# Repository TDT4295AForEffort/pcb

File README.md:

# pcb
The greenest pcb in the west

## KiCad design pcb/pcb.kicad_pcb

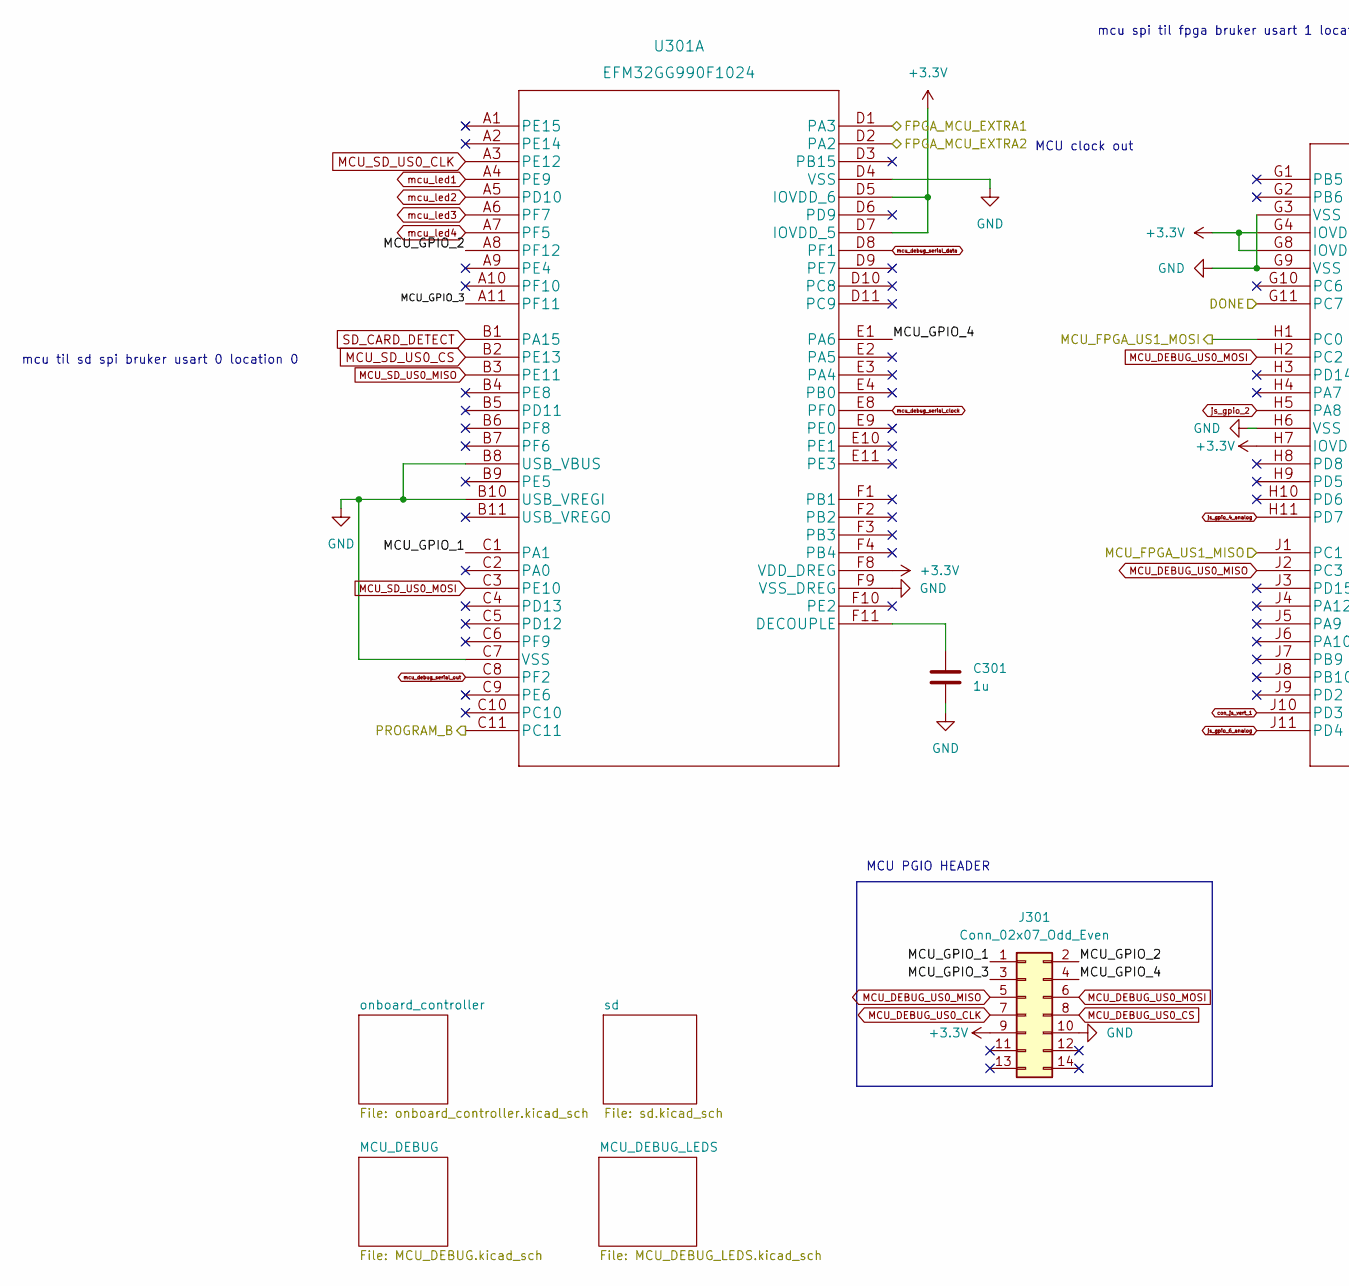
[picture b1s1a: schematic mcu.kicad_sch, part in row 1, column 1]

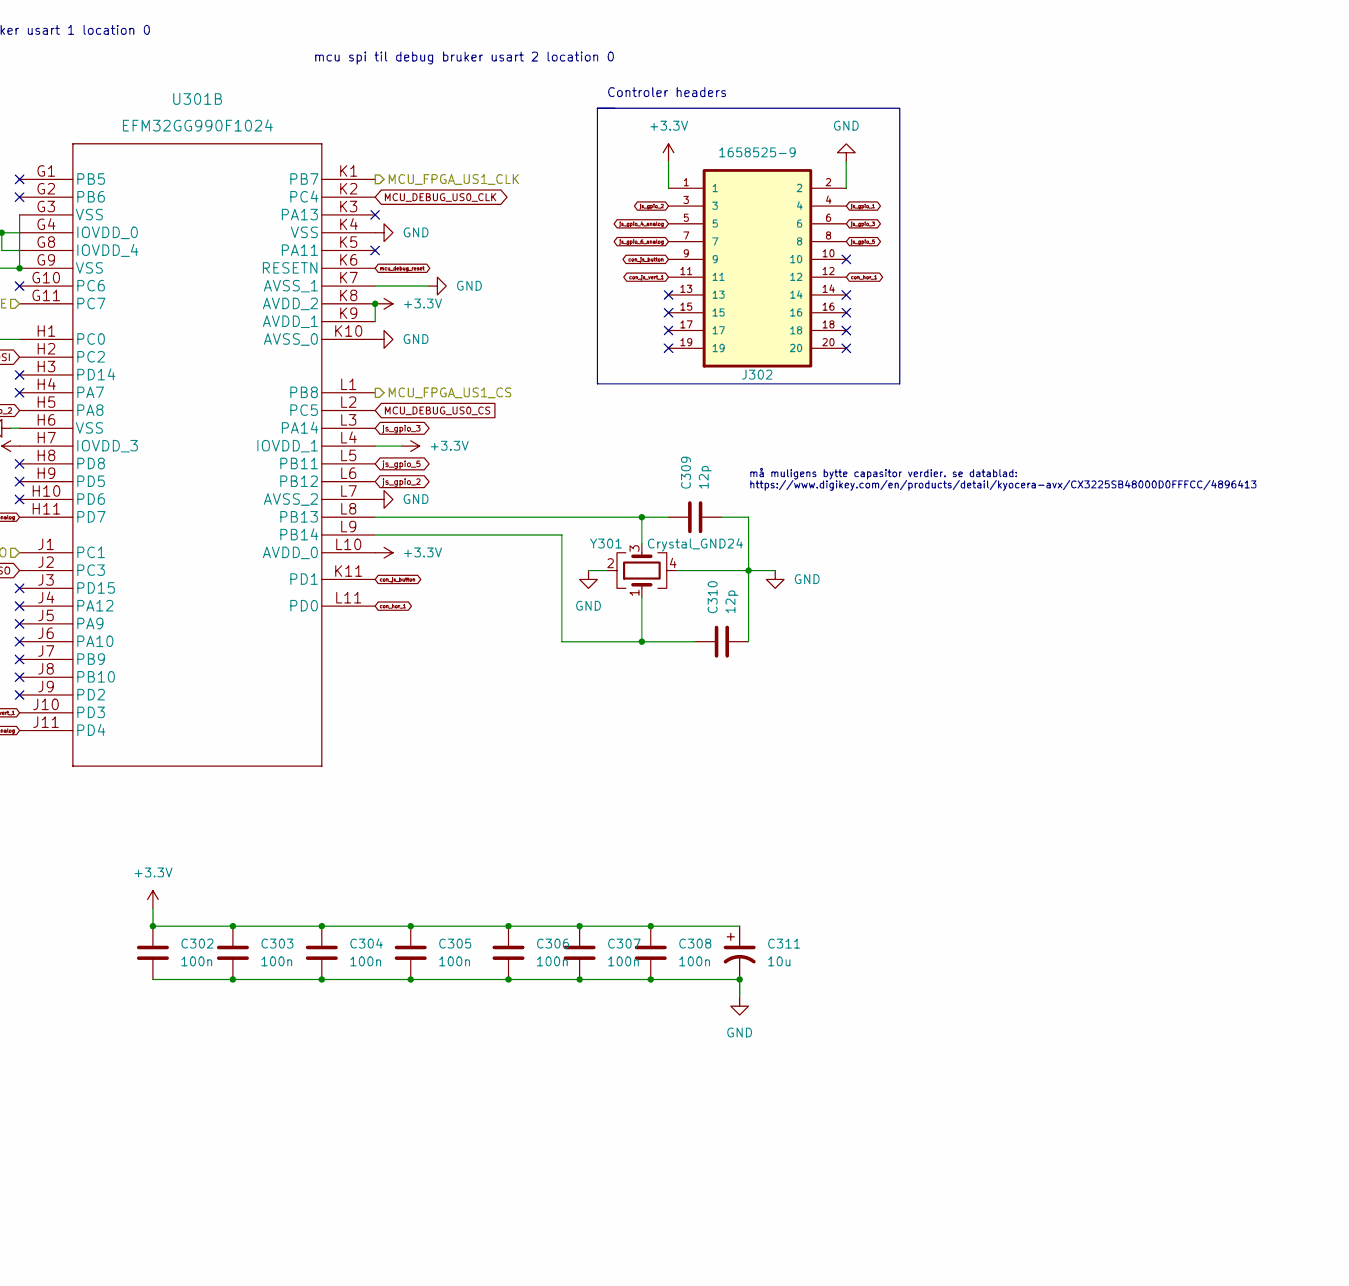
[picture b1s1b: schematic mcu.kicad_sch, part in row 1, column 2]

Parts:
C301: 1u; C_0805_2012Metric_Pad1.18x1.45mm_HandSolder
C302, C303, C304, C305, C306, C307, C308: 100n; C_0805_2012Metric_Pad1.18x1.45mm_HandSolder
C309, C310: 12p; C_0603_1608Metric_Pad1.08x0.95mm_HandSolder
C311: 10u; C_0805_2012Metric_Pad1.18x1.45mm_HandSolder
J301: Conn_02x07_Odd_Even; PinHeader_2x07_P2.54mm_Vertical
J302: 1658525-9; TE_1658525-9
U301: EFM32GG990F1024
Y301: Crystal_GND24; OSC_ECS-2520S25-250-FN-TR

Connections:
+3.3V: C302.1, C303.1, C304.1, C305.1, C306.1, C307.1, C308.1, C311.1, J301.9, J302.1, U301.D5 (IOVDD_6), U301.D7 (IOVDD_5), U301.F8 (VDD_DREG), U301.G4 (IOVDD_0), U301.G8 (IOVDD_4), U301.H7 (IOVDD_3), U301.K8 (AVDD_2), U301.K9 (AVDD_1), U301.L4 (IOVDD_1), U301.L10 (AVDD_0); also elsewhere on the board
/Mcu/MCU_GPIO_1: J301.1, U301.C1 (PA1)
/Mcu/MCU_GPIO_2: J301.2, U301.A8 (PF12)
/Mcu/MCU_GPIO_3: J301.3, U301.A11 (PF11)
/Mcu/MCU_GPIO_4: J301.4, U301.E1 (PA6)
FGPA_MCU_EXTRA1: U301.D1 (PA3); also elsewhere on the board
FGPA_MCU_EXTRA2: U301.D2 (PA2); also elsewhere on the board
FGPA_MCU_SPI_CLK: U301.K1 (PB7); also elsewhere on the board
FGPA_MCU_SPI_CS: U301.L1 (PB8); also elsewhere on the board
FGPA_MCU_SPI_SDI: U301.H1 (PC0); also elsewhere on the board
FGPA_MCU_SPI_SDO: U301.J1 (PC1); also elsewhere on the board
FPGA_DONE: U301.G11 (PC7); also elsewhere on the board
FPGA_PROGRAM_B: U301.C11; also elsewhere on the board
GND: C301.2, C302.2, C303.2, C304.2, C305.2, C306.2, C307.2, C308.2, C309.2, C310.2, C311.2, J301.10, J302.2, U301.B8 (USB_VBUS), U301.B10 (USB_VREGI), U301.C7 (VSS), U301.D4 (VSS), U301.F9 (VSS_DREG), U301.G3 (VSS), U301.G9 (VSS), U301.H6 (VSS), U301.K4 (VSS), U301.K7 (AVSS_1), U301.K10 (AVSS_0), U301.L7 (AVSS_2), Y301.2, Y301.4; also elsewhere on the board
MCU_DEBUG_US0_CLK: J301.7, U301.K2 (PC4)
MCU_DEBUG_US0_CS: J301.8, U301.L2 (PC5)
MCU_DEBUG_US0_MISO: J301.5, U301.J2 (PC3)
MCU_DEBUG_US0_MOSI: J301.6, U301.H2 (PC2)
MCU_SD_US0_CLK: U301.A3 (PE12); also elsewhere on the board
MCU_SD_US0_CS: U301.B2 (PE13); also elsewhere on the board
MCU_SD_US0_MISO: U301.B3 (PE11); also elsewhere on the board
MCU_SD_US0_MOSI: U301.C3 (PE10); also elsewhere on the board
unnamed: C301.1, U301.F11 (DECOUPLE)
unnamed: C309.1, U301.L8 (PB13), Y301.3
unnamed: C310.1, U301.L9 (PB14), Y301.1
SD_CARD_DETECT: U301.B1 (PA15); also elsewhere on the board
con_hor_1: J302.12, U301.L11 (PD0)
con_js_button: J302.9, U301.K11 (PD1)
con_js_vert_1: J302.11, U301.J10 (PD3)
js_gpio_3: J302.6, U301.L3 (PA14)
js_gpio_4_analog: J302.5, U301.H11 (PD7)
js_gpio_5: J302.8, U301.L5 (PB11)
js_gpio_6_analog: J302.7, U301.J11 (PD4)
mcu_debug_reset: U301.K6 (RESETN); also elsewhere on the board
mcu_debug_serial_clock: U301.E8 (PF0); also elsewhere on the board
mcu_debug_serial_data: U301.D8 (PF1); also elsewhere on the board
mcu_debug_serial_out: U301.C8 (PF2); also elsewhere on the board
mcu_led1: U301.A4 (PE9); also elsewhere on the board
mcu_led2: U301.A5 (PD10); also elsewhere on the board
mcu_led3: U301.A6 (PF7); also elsewhere on the board
mcu_led4: U301.A7 (PF5); also elsewhere on the board

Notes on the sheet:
mcu til sd spi bruker usart 0 location 0
MCU PGIO HEADER
mcu spi til debug bruker usart 2 location 0
Controler headers
må muligens bytte capasitor verdier. se datablad: https://www.digikey.com/en/products/detail/kyocera-avx/CX3225SB48000D0FFFCC/4896413
MCU clock out
mcu spi til fpga bruker usart 1 location 0

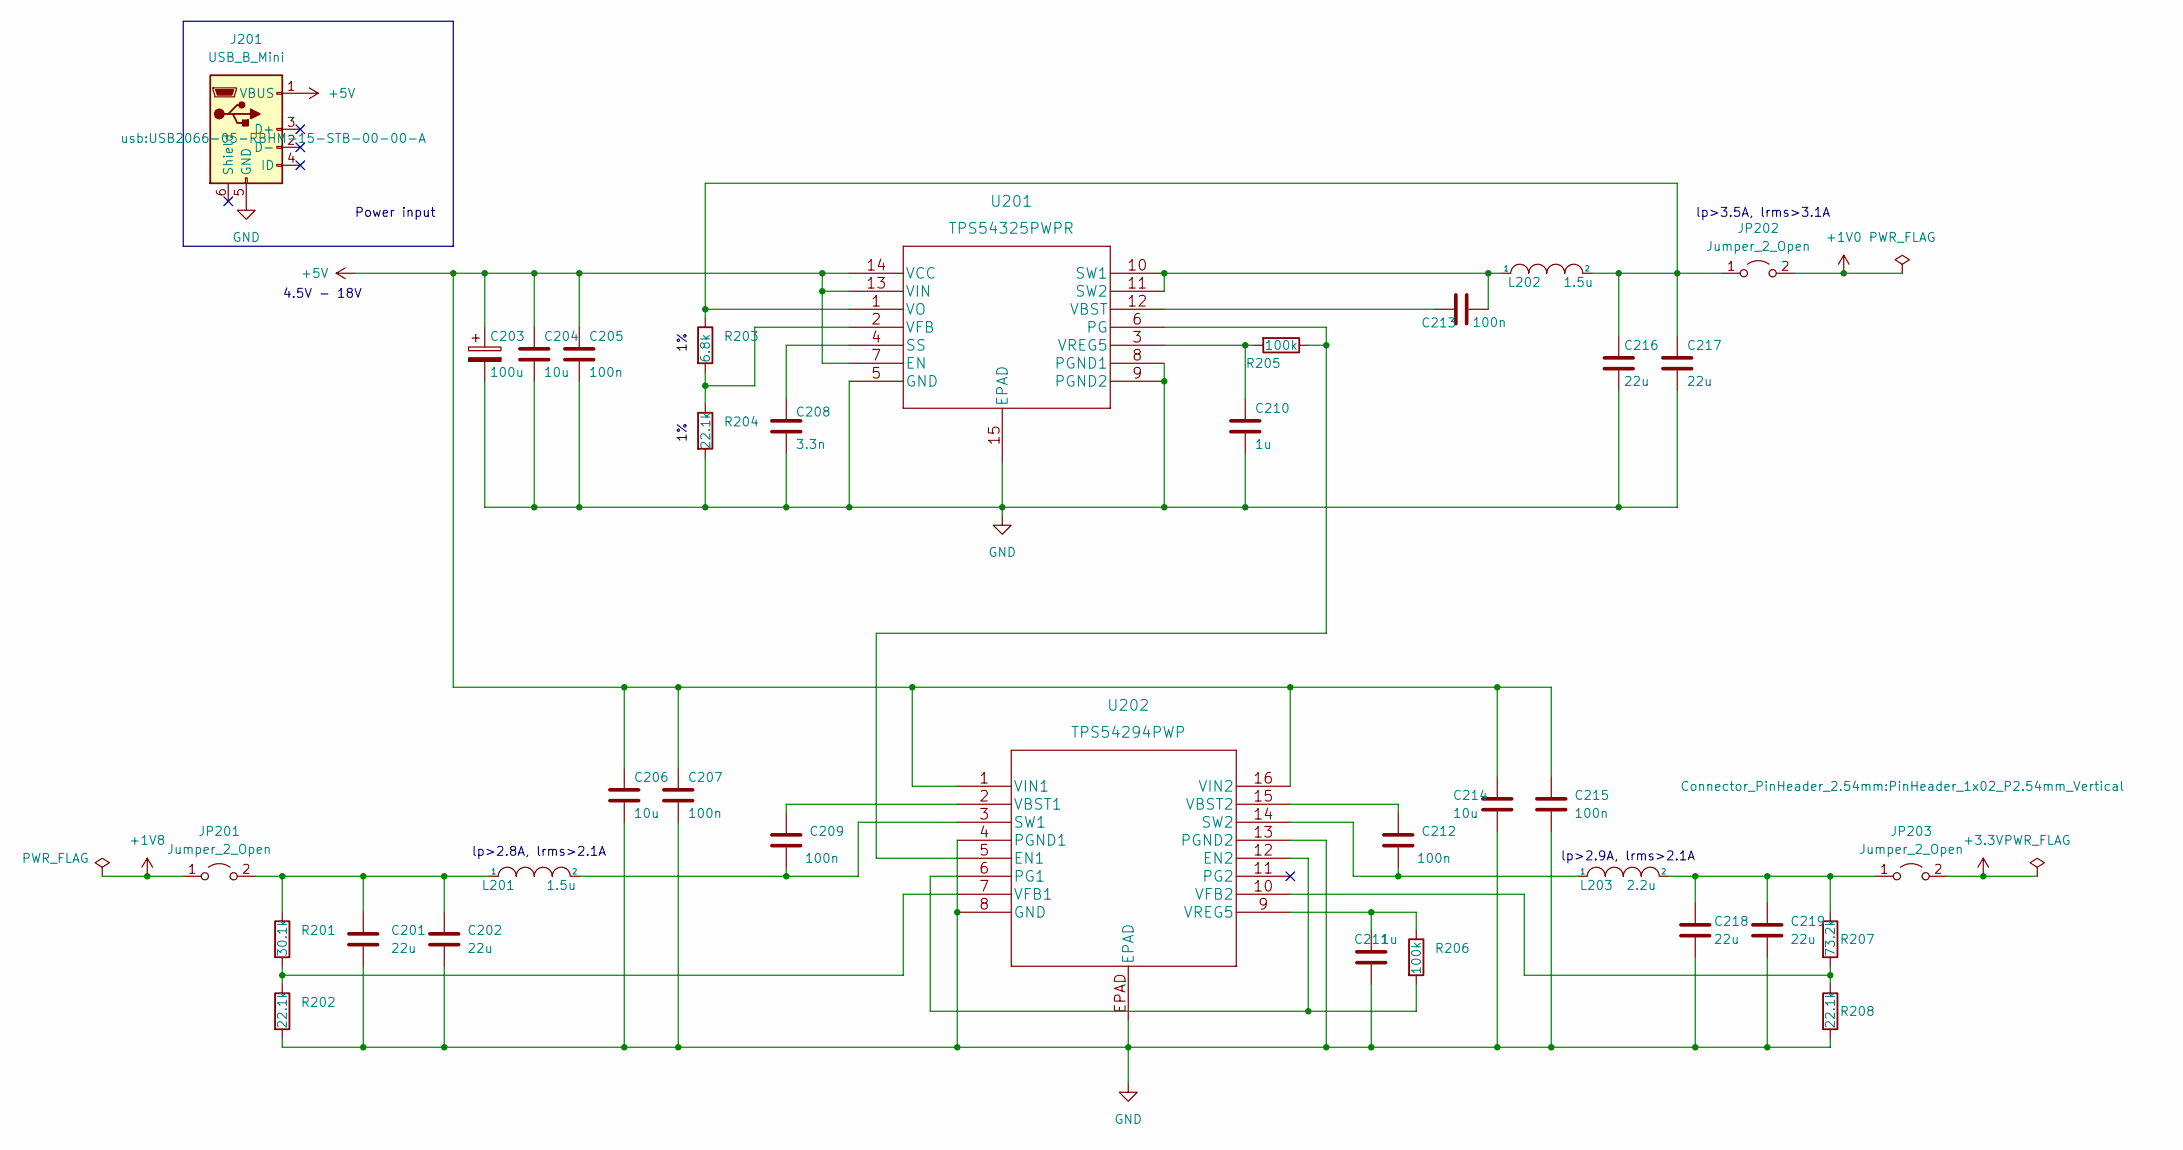
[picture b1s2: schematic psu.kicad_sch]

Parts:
C201, C202, C216, C217, C218, C219: 22u; C_0805_2012Metric_Pad1.18x1.45mm_HandSolder
C203: 100u; C_1210_3225Metric_Pad1.33x2.70mm_HandSolder
C204, C206, C214: 10u; C_0805_2012Metric_Pad1.18x1.45mm_HandSolder
C205, C207, C209, C212, C213, C215: 100n; C_0805_2012Metric_Pad1.18x1.45mm_HandSolder
C208: 3.3n; C_0805_2012Metric_Pad1.18x1.45mm_HandSolder
C210, C211: 1u; C_0805_2012Metric_Pad1.18x1.45mm_HandSolder
J201: USB_B_Mini; USB2066-05-RBHM-15-STB-00-00-A
JP201, JP202, JP203: Jumper_2_Open; PinHeader_1x02_P2.54mm_Vertical
L201, L202: 1.5u; L_1210_3225Metric_Pad1.42x2.65mm_HandSolder
L203: 2.2u; L_1210_3225Metric_Pad1.42x2.65mm_HandSolder
R201: 30.1k; R_0805_2012Metric_Pad1.20x1.40mm_HandSolder
R202, R204, R208: 22.1k; R_0805_2012Metric_Pad1.20x1.40mm_HandSolder
R203: 6.8k; R_0805_2012Metric_Pad1.20x1.40mm_HandSolder
R205, R206: 100k; R_0805_2012Metric_Pad1.20x1.40mm_HandSolder
R207: 73.2k; R_0805_2012Metric_Pad1.20x1.40mm_HandSolder
U201: TPS54325PWPR
U202: TPS54294PWP

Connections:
+1V0: JP202.2 (B); also elsewhere on the board
+1V8: JP201.1 (A); also elsewhere on the board
+3.3V: JP203.2 (B); also elsewhere on the board
+5V: C203.1, C204.1, C205.1, C206.1, C207.1, C214.1, C215.1, J201.1 (VBUS), U201.7 (EN), U201.13 (VIN), U201.14 (VCC), U202.1 (VIN1), U202.16 (VIN2)
GND: C201.2, C202.2, C203.2, C204.2, C205.2, C206.2, C207.2, C208.2, C210.2, C211.2, C214.2, C215.2, C216.2, C217.2, C218.2, C219.2, J201.5 (GND), R202.2, R204.2, R208.2, U201.5 (GND), U201.8 (PGND1), U201.9 (PGND2), U201.15 (EPAD), U202.4 (PGND1), U202.8 (GND), U202.13 (PGND2), U202.EPAD, U202.V; also elsewhere on the board
unnamed: C201.1, C202.1, JP201.2 (B), L201.1, R201.1
unnamed: C208.1, U201.4 (SS)
unnamed: C209.1, U202.2 (VBST1)
unnamed: C209.2, L201.2, U202.3 (SW1)
unnamed: C210.1, R205.2, U201.3 (VREG5)
unnamed: C211.1, R206.1, U202.9 (VREG5)
unnamed: C212.1, U202.15 (VBST2)
unnamed: C212.2, L203.1, U202.14 (SW2)
unnamed: C213.1, U201.12 (VBST)
unnamed: C213.2, L202.1, U201.10 (SW1), U201.11 (SW2)
unnamed: C216.1, C217.1, JP202.1 (A), L202.2, R203.1, U201.1 (VO)
unnamed: C218.1, C219.1, JP203.1 (A), L203.2, R207.1
unnamed: R201.2, R202.1, U202.7 (VFB1)
unnamed: R203.2, R204.1, U201.2 (VFB)
unnamed: R205.1, U201.6 (PG), U202.5 (EN1)
unnamed: R206.2, U202.6 (PG1), U202.12 (EN2)
unnamed: R207.2, R208.1, U202.10 (VFB2)

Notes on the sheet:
lp>3.5A, lrms>3.1A
4.5V - 18V
lp>2.9A, lrms>2.1A
Power input
lp>2.8A, lrms>2.1A

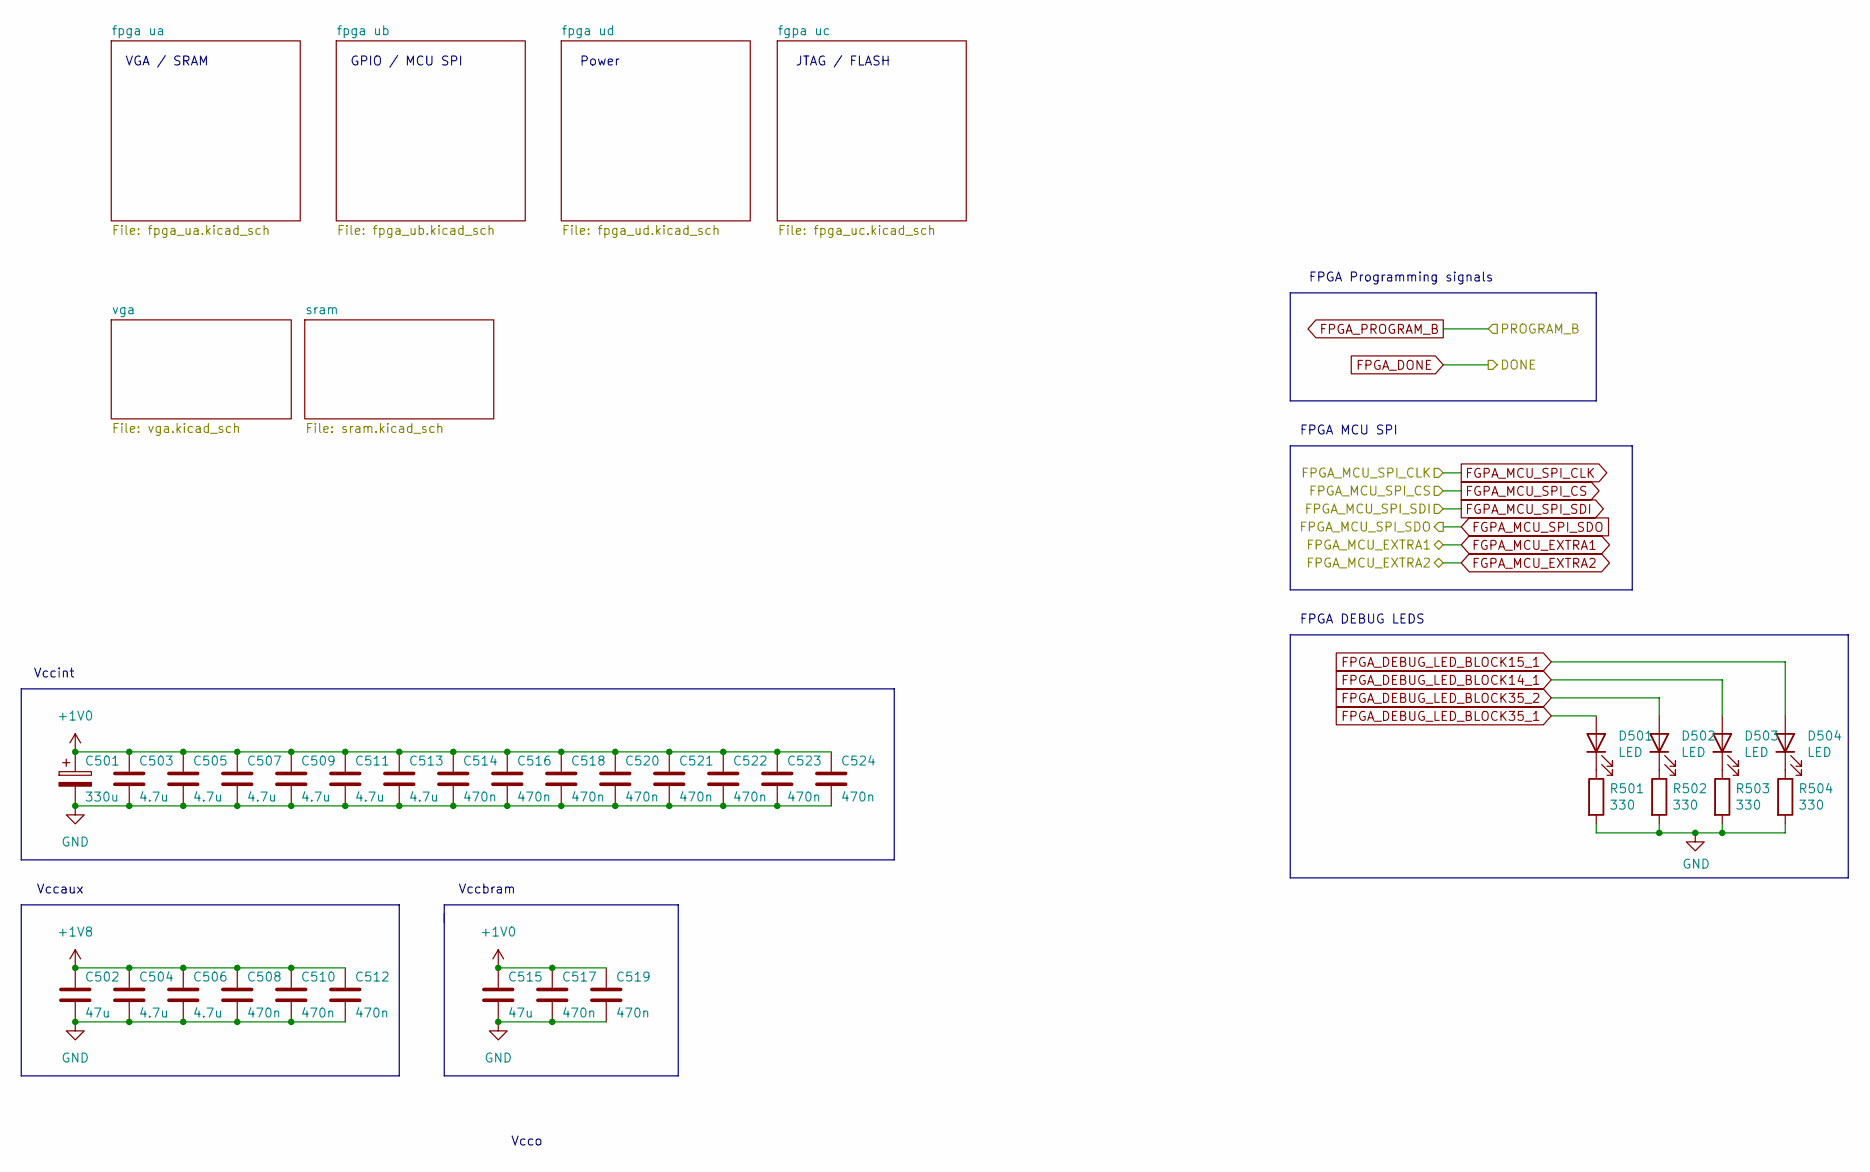
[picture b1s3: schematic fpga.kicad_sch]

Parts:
C501: 330u; T520V337M2R5ATE025
C502, C515: 47u; C_1210_3225Metric_Pad1.33x2.70mm_HandSolder
C503, C504, C505, C506, C507, C509, C511, C513: 4.7u; C_0805_2012Metric_Pad1.18x1.45mm_HandSolder
C508, C510, C512, C514, C516, C517, C518, C519, C520, C521, C522, C523, C524: 470n; C_0603_1608Metric_Pad1.08x0.95mm_HandSolder
D501, D502, D503, D504: LED; LED_1206_3216Metric_Pad1.42x1.75mm_HandSolder
R501, R502, R503, R504: 330; R_0805_2012Metric_Pad1.20x1.40mm_HandSolder

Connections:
+1V0: C501.1, C503.1, C505.1, C507.1, C509.1, C511.1, C513.1, C514.1, C515.1, C516.1, C517.1, C518.1, C519.1, C520.1, C521.1, C522.1, C523.1, C524.1; also elsewhere on the board
+1V8: C502.1, C504.1, C506.1, C508.1, C510.1, C512.1; also elsewhere on the board
FPGA_DEBUG_LED_BLOCK14_1: D503.2 (A); also elsewhere on the board
FPGA_DEBUG_LED_BLOCK15_1: D504.2 (A); also elsewhere on the board
FPGA_DEBUG_LED_BLOCK35_1: D501.2 (A); also elsewhere on the board
FPGA_DEBUG_LED_BLOCK35_2: D502.2 (A); also elsewhere on the board
GND: C501.2, C502.2, C503.2, C504.2, C505.2, C506.2, C507.2, C508.2, C509.2, C510.2, C511.2, C512.2, C513.2, C514.2, C515.2, C516.2, C517.2, C518.2, C519.2, C520.2, C521.2, C522.2, C523.2, C524.2, R501.2, R502.2, R503.2, R504.2; also elsewhere on the board
unnamed: D501.1 (K), R501.1
unnamed: D502.1 (K), R502.1
unnamed: D503.1 (K), R503.1
unnamed: D504.1 (K), R504.1

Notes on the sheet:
FPGA Programming signals
Vccint
Power
Vccaux
Vcco
FPGA MCU SPI
JTAG / FLASH
GPIO / MCU SPI
Vccbram
VGA / SRAM
FPGA DEBUG LEDS

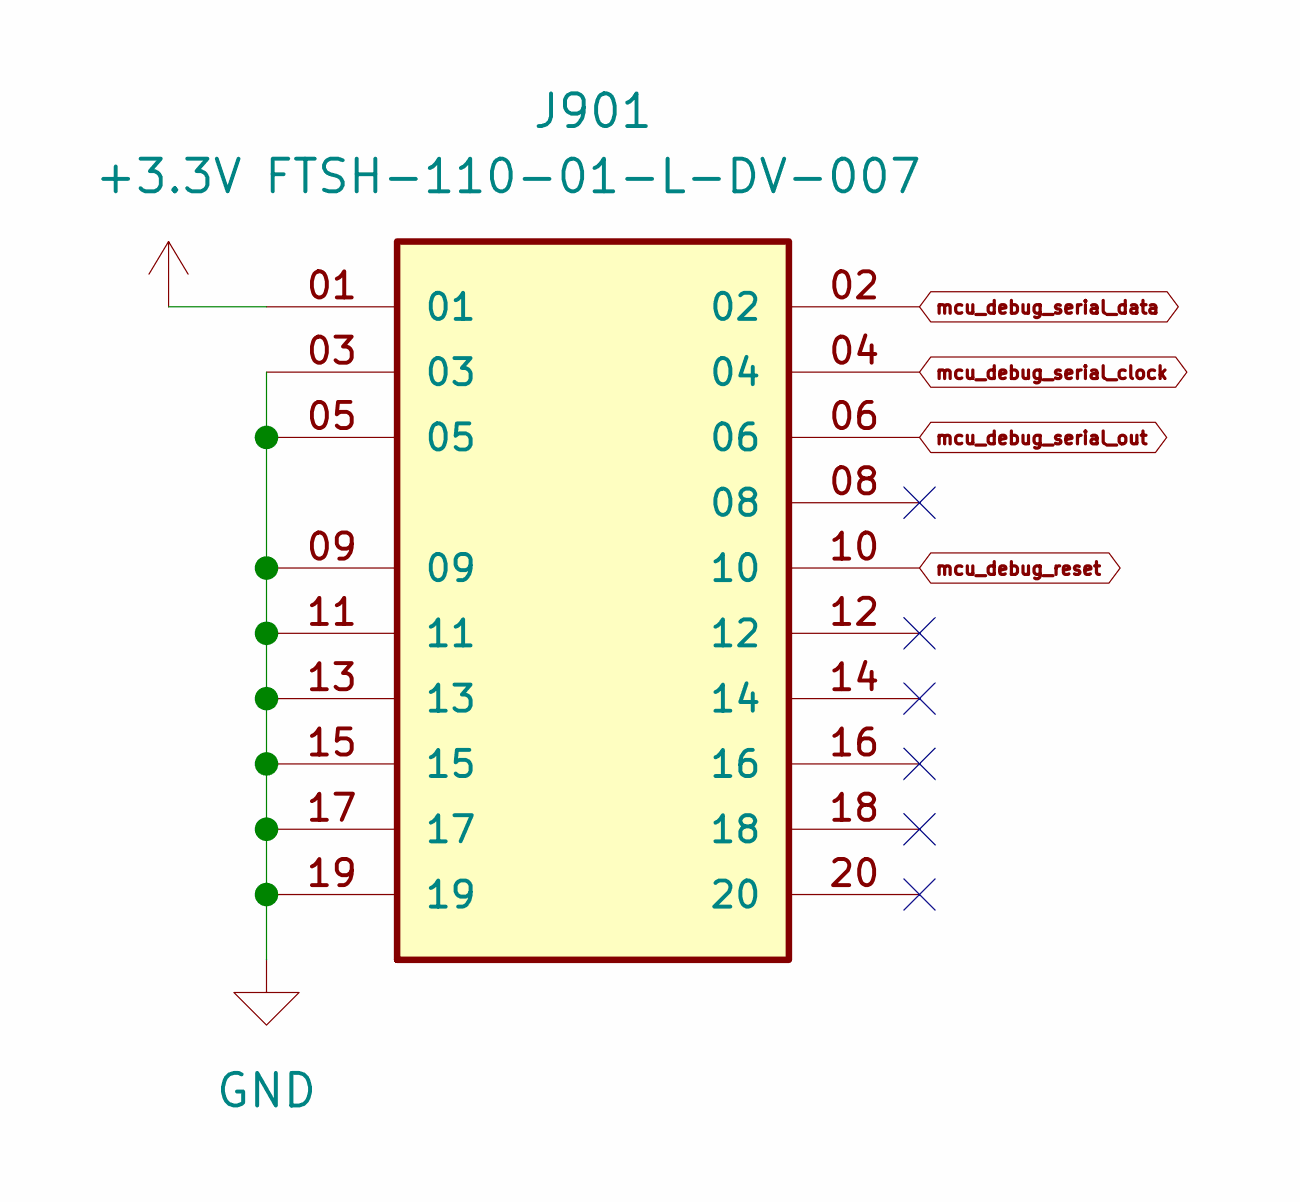
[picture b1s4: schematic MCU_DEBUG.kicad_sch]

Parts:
J901: FTSH-110-01-L-DV-007; SAMTEC_FTSH-110-01-L-DV-007; PARTREV R

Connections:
+3.3V: J901.01; also elsewhere on the board
GND: J901.03, J901.05, J901.09, J901.11, J901.13, J901.15, J901.17, J901.19; also elsewhere on the board
mcu_debug_reset: J901.10; also elsewhere on the board
mcu_debug_serial_clock: J901.04; also elsewhere on the board
mcu_debug_serial_data: J901.02; also elsewhere on the board
mcu_debug_serial_out: J901.06; also elsewhere on the board

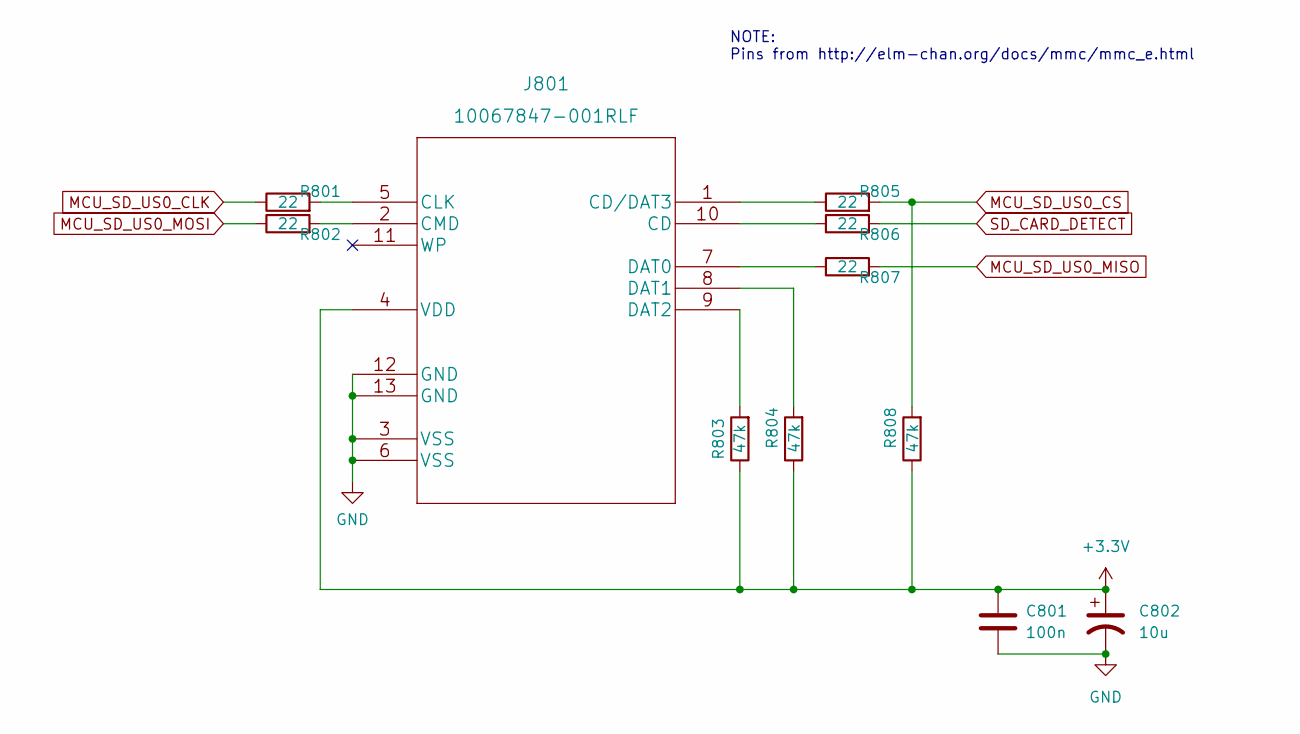
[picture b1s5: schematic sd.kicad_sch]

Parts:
C801: 100n; C_0805_2012Metric_Pad1.18x1.45mm_HandSolder
C802: 10u; C_0805_2012Metric_Pad1.18x1.45mm_HandSolder
J801: 10067847-001RLF
R801, R802, R805, R806, R807: 22; R_0805_2012Metric_Pad1.20x1.40mm_HandSolder
R803, R804, R808: 47k; R_0805_2012Metric_Pad1.20x1.40mm_HandSolder

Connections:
+3.3V: C801.1, C802.1, J801.4 (VDD), R803.1, R804.1, R808.1; also elsewhere on the board
GND: C801.2, C802.2, J801.3 (VSS), J801.6 (VSS), J801.12 (GND), J801.13 (GND); also elsewhere on the board
MCU_SD_US0_CLK: R801.1; also elsewhere on the board
MCU_SD_US0_CS: R805.2, R808.2; also elsewhere on the board
MCU_SD_US0_MISO: R807.2; also elsewhere on the board
MCU_SD_US0_MOSI: R802.1; also elsewhere on the board
unnamed: J801.1 (CD/DAT3), R805.1
unnamed: J801.2 (CMD), R802.2
unnamed: J801.5 (CLK), R801.2
unnamed: J801.7 (DAT0), R807.1
unnamed: J801.8 (DAT1), R804.2
unnamed: J801.9 (DAT2), R803.2
unnamed: J801.10 (CD), R806.1
SD_CARD_DETECT: R806.2; also elsewhere on the board

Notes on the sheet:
NOTE: Pins from http://elm-chan.org/docs/mmc/mmc_e.html

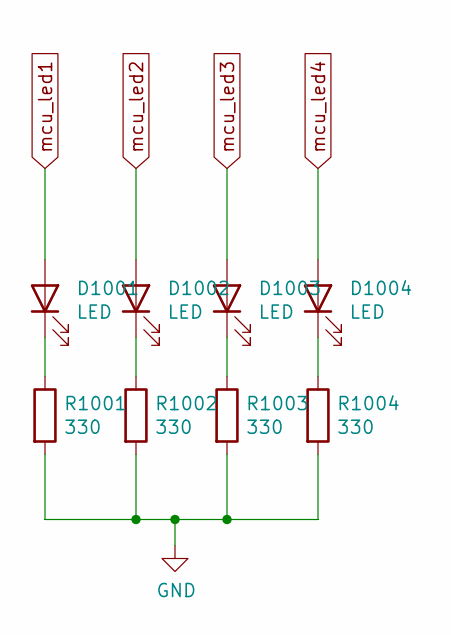
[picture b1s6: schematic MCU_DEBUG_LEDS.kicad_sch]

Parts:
D1001, D1002, D1003, D1004: LED; LED_1206_3216Metric_Pad1.42x1.75mm_HandSolder
R1001, R1002, R1003, R1004: 330; R_0805_2012Metric_Pad1.20x1.40mm_HandSolder

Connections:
GND: R1001.2, R1002.2, R1003.2, R1004.2; also elsewhere on the board
unnamed: D1001.1 (K), R1001.1
unnamed: D1002.1 (K), R1002.1
unnamed: D1003.1 (K), R1003.1
unnamed: D1004.1 (K), R1004.1
mcu_led1: D1001.2 (A); also elsewhere on the board
mcu_led2: D1002.2 (A); also elsewhere on the board
mcu_led3: D1003.2 (A); also elsewhere on the board
mcu_led4: D1004.2 (A); also elsewhere on the board

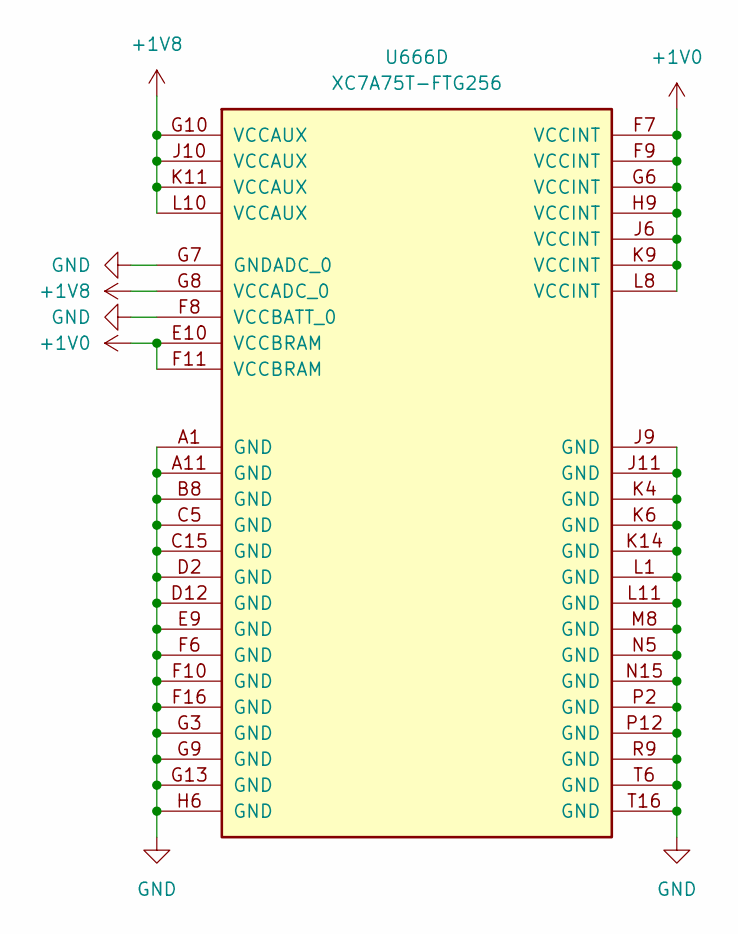
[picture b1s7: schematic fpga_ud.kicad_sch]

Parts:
U666: XC7A75T-FTG256; Xilinx_FTG256

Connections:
+1V0: U666.E10 (VCCBRAM), U666.F7 (VCCINT), U666.F9 (VCCINT), U666.F11 (VCCBRAM), U666.G6 (VCCINT), U666.H9 (VCCINT), U666.J6 (VCCINT), U666.K9 (VCCINT), U666.L8 (VCCINT); also elsewhere on the board
+1V8: U666.G8 (VCCADC_0), U666.G10 (VCCAUX), U666.J10 (VCCAUX), U666.K11 (VCCAUX), U666.L10 (VCCAUX); also elsewhere on the board
GND: U666.A1 (GND), U666.A11 (GND), U666.B8 (GND), U666.C5 (GND), U666.C15 (GND), U666.D2 (GND), U666.D12 (GND), U666.E9 (GND), U666.F6 (GND), U666.F8 (VCCBATT_0), U666.F10 (GND), U666.F16 (GND), U666.G3 (GND), U666.G7 (GNDADC_0), U666.G9 (GND), U666.G13 (GND), U666.H6 (GND), U666.J9 (GND), U666.J11 (GND), U666.K4 (GND), U666.K6 (GND), U666.K14 (GND), U666.L1 (GND), U666.L11 (GND), U666.M8 (GND), U666.N5 (GND), U666.N15 (GND), U666.P2 (GND), U666.P12 (GND), U666.R9 (GND), U666.T6 (GND), U666.T16 (GND); also elsewhere on the board

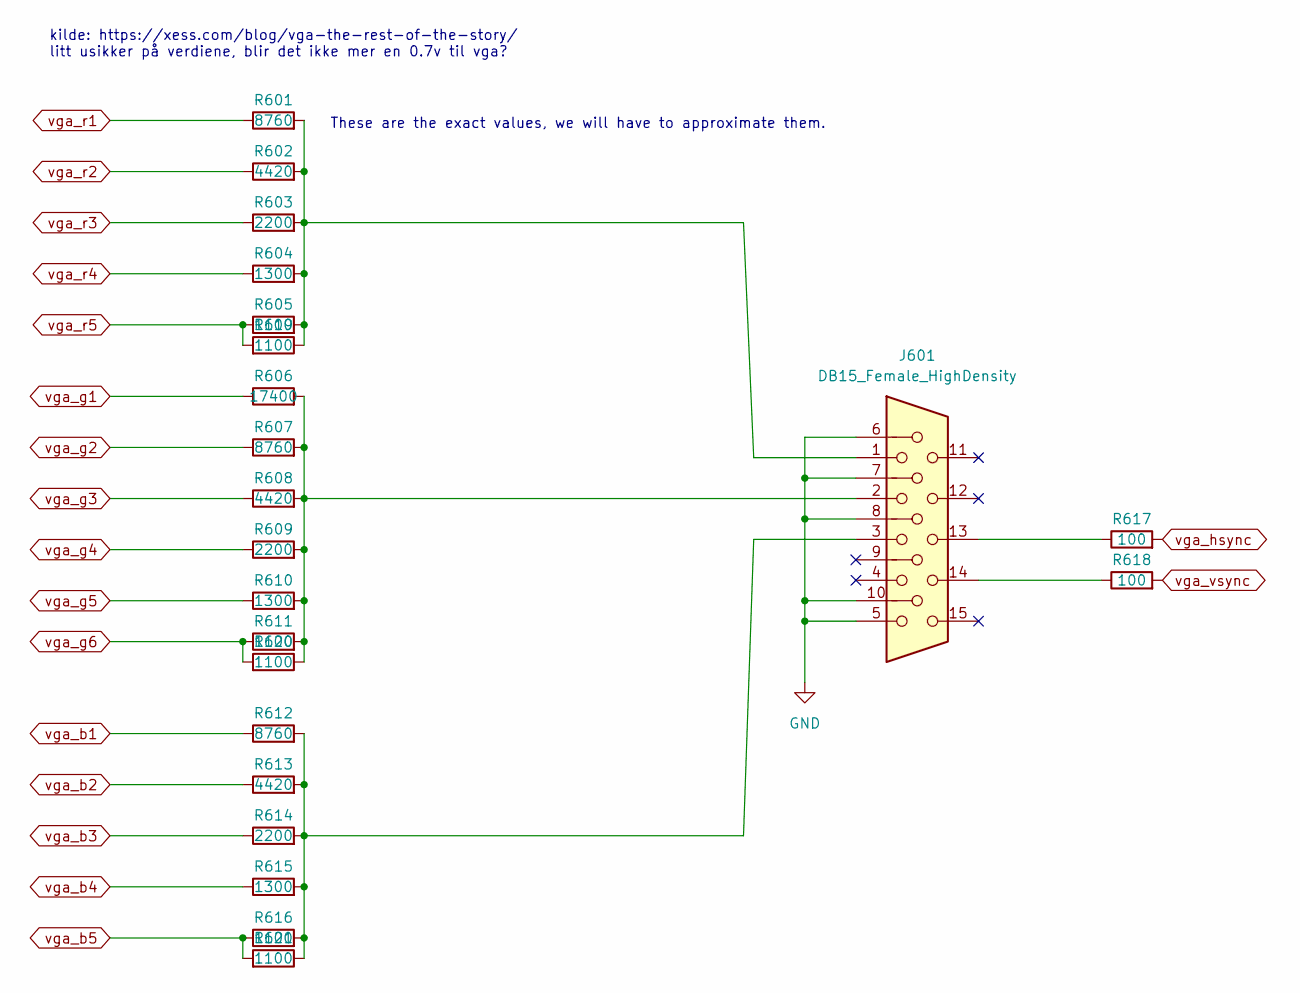
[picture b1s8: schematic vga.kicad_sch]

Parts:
J601: DB15_Female_HighDensity; AHDF15A-KG-TAXB
R601, R607, R612: 8760; R_0805_2012Metric_Pad1.20x1.40mm_HandSolder
R602, R608, R613: 4420; R_0603_1608Metric_Pad0.98x0.95mm_HandSolder
R603, R609, R614: 2200; R_0603_1608Metric_Pad0.98x0.95mm_HandSolder
R604, R610, R615: 1300; R_0603_1608Metric_Pad0.98x0.95mm_HandSolder
R605, R611, R616, R619, R620, R621: 1100; R_0603_1608Metric_Pad0.98x0.95mm_HandSolder
R606: 17400; R_0603_1608Metric_Pad0.98x0.95mm_HandSolder
R617, R618: 100; R_0805_2012Metric_Pad1.20x1.40mm_HandSolder

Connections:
GND: J601.5, J601.6, J601.7, J601.8, J601.10; also elsewhere on the board
unnamed: J601.1, R601.2, R602.2, R603.2, R604.2, R605.2, R619.1
unnamed: J601.2, R606.2, R607.2, R608.2, R609.2, R610.2, R611.2, R620.1
unnamed: J601.3, R612.2, R613.2, R614.2, R615.2, R616.2, R621.1
unnamed: J601.13, R617.1
unnamed: J601.14, R618.1
vga_b1: R612.1; also elsewhere on the board
vga_b2: R613.1; also elsewhere on the board
vga_b3: R614.1; also elsewhere on the board
vga_b4: R615.1; also elsewhere on the board
vga_b5: R616.1, R621.2; also elsewhere on the board
vga_g1: R606.1; also elsewhere on the board
vga_g2: R607.1; also elsewhere on the board
vga_g3: R608.1; also elsewhere on the board
vga_g4: R609.1; also elsewhere on the board
vga_g5: R610.1; also elsewhere on the board
vga_g6: R611.1, R620.2; also elsewhere on the board
vga_hsync: R617.2; also elsewhere on the board
vga_r1: R601.1; also elsewhere on the board
vga_r2: R602.1; also elsewhere on the board
vga_r3: R603.1; also elsewhere on the board
vga_r4: R604.1; also elsewhere on the board
vga_r5: R605.1, R619.2; also elsewhere on the board
vga_vsync: R618.2; also elsewhere on the board

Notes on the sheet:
These are the exact values, we will have to approximate them.
kilde: https://xess.com/blog/vga-the-rest-of-the-story/ litt usikker på verdiene, blir det ikke mer en 0.7v til vga?

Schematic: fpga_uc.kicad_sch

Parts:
C1401: 47u; C_1210_3225Metric_Pad1.33x2.70mm_HandSolder
C1402: 100u; C_1210_3225Metric_Pad1.33x2.70mm_HandSolder
J1401: FPGA_JTAG; PinHeader_2x07_P2.54mm_Vertical
R1401, R1402, R1407, R1408: 4.7k; R_0805_2012Metric_Pad1.20x1.40mm_HandSolder
R1403: 330; R_0805_2012Metric_Pad1.20x1.40mm_HandSolder
R1404, R1405: 10k; R_0805_2012Metric_Pad1.20x1.40mm_HandSolder
R1406: 2.4k; R_0805_2012Metric_Pad1.20x1.40mm_HandSolder
U666: XC7A75T-FTG256; Xilinx_FTG256
U1402: S25FL127SABMFV101

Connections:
+3.3V: C1401.1, C1402.1, J1401.2, R1401.1, R1402.1, R1403.1, R1404.1, R1405.1, R1406.1, R1407.2, R1408.2, U666.E7 (CFGBVS_0), U666.L6 (VCCO_0), U666.M9 (M0_0), U1402.8 (VCC); also elsewhere on the board
FPGA_DONE: R1403.2, U666.H10 (DONE_0); also elsewhere on the board
FPGA_FLASH_D00_IO0: U1402.5 (SI/IO0); also elsewhere on the board
FPGA_FLASH_D01_IO1: U1402.2 (SO/IO1); also elsewhere on the board
FPGA_FLASH_D02_IO2: R1407.1, U1402.3 (*WP/IO2); also elsewhere on the board
FPGA_FLASH_D03_IO3: R1408.1, U1402.7 (*HOLD/IO3); also elsewhere on the board
FPGA_FLASH_FCSB_CS: R1406.2, U1402.1 (*CS); also elsewhere on the board
FPGA_PROGRAM_B: R1401.2, U666.L9 (PROGRAM_B_0); also elsewhere on the board
GND: C1401.2, C1402.2, J1401.1, J1401.3, J1401.5, J1401.7, J1401.9, J1401.11, J1401.13, U666.H7 (VREFN_0), U666.H8 (VP_0), U666.J7 (VN_0), U666.J8 (VREFP_0), U666.M10 (M1_0), U666.M11 (M2_0), U1402.4 (GND); also elsewhere on the board
unnamed: J1401.4, R1404.2, U666.M7 (TMS_0)
unnamed: J1401.6, R1405.2, U666.L7 (TCK_0)
unnamed: J1401.8, U666.N8 (TDO_0)
unnamed: J1401.10, U666.N7 (TDI_0)
unnamed: R1402.2, U666.K10 (INIT_B_0)
unnamed: U666.E8 (CCLK_0), U1402.6 (CLK)

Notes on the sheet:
Clock from FPGA to flash
FPGA Flash Memory
TODO - connect labels to FPGA
JTAG
NOTE - Using 'Quad' configuration for Flash Memory

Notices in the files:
parts and their libraries:
Copyright 2021 Accelerated Designs. All rights reserved.
